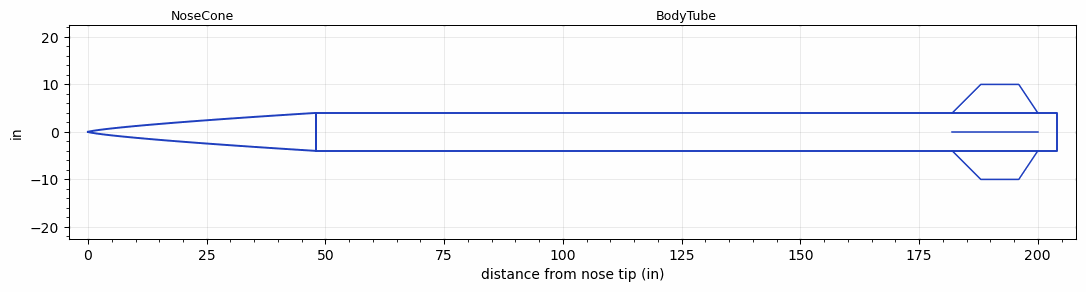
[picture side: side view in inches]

<RASAeroDocument>
 <FileVersion>2</FileVersion>
 <RocketDesign>
  <NoseCone>
   <Length>48</Length>
   <Diameter>8</Diameter>
   <Shape>Power Law</Shape>
   <Location>0</Location>
   <PowerLaw>0.75</PowerLaw>
  </NoseCone>
  <BodyTube>
   <Length>156</Length>
   <Diameter>8</Diameter>
   <Location>48</Location>
   <Fin>
    <Count>4</Count>
    <Chord>18</Chord>
    <Span>6</Span>
    <SweepDistance>6</SweepDistance>
    <TipChord>8</TipChord>
    <Thickness>0.5</Thickness>
    <Location>22</Location>
    <AirfoilSection>Rounded</AirfoilSection>
   </Fin>
  </BodyTube>
  <Surface>Smooth (Zero Roughness)</Surface>
  <ModifiedBarrowman>False</ModifiedBarrowman>
  <Turbulence>False</Turbulence>
  <UseBooster1>False</UseBooster1>
  <UseBooster2>False</UseBooster2>
 </RocketDesign>
 <LaunchSite>
  <Altitude>0</Altitude>
  <Pressure>0</Pressure>
  <RodAngle>0</RodAngle>
  <RodLength>4</RodLength>
  <Temperature>74</Temperature>
  <WindSpeed>0</WindSpeed>
 </LaunchSite>
 <Recovery>
  <Altitude1>1000</Altitude1>
  <Altitude2>1000</Altitude2>
  <DeviceType1>None</DeviceType1>
  <DeviceType2>None</DeviceType2>
  <Event1>False</Event1>
  <Event2>False</Event2>
  <Size1>1</Size1>
  <Size2>1</Size2>
  <EventType1>None</EventType1>
  <EventType2>None</EventType2>
  <CD1>1.33</CD1>
  <CD2>1.33</CD2>
 </Recovery>
 <SimulationList>
  <Simulation>
   <SustainerEngine>Q19135  (TRC)</SustainerEngine>
   <SustainerLaunchWt>300</SustainerLaunchWt>
   <SustainerNozzleDiameter>6.75</SustainerNozzleDiameter>
   <SustainerCG>80</SustainerCG>
   <SustainerIgnitionDelay>0</SustainerIgnitionDelay>
   <Booster1SeparationDelay>0</Booster1SeparationDelay>
   <Booster1IgnitionDelay>0</Booster1IgnitionDelay>
   <IncludeBooster1>False</IncludeBooster1>
   <Booster2Delay>0</Booster2Delay>
   <IncludeBooster2>False</IncludeBooster2>
   <MaxVelocity>312.478</MaxVelocity>
   <OptimumWt>300</OptimumWt>
   <OptimumMaxAlt>300</OptimumMaxAlt>
  </Simulation>
 </SimulationList>
</RASAeroDocument>
